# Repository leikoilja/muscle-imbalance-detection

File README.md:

<!-- PROJECT SHIELDS -->
<!--
*** I'm using markdown "reference style" links for readability.
*** Reference links are enclosed in brackets [ ] instead of parentheses ( ).
*** See the bottom of this document for the declaration of the reference variables
*** for contributors-url, forks-url, etc. This is an optional, concise syntax you may use.
*** https://www.markdownguide.org/basic-syntax/#reference-style-links
-->
[![Contributors][contributors-shield]][contributors-url]
[![Forks][forks-shield]][forks-url]
[![Stargazers][stars-shield]][stars-url]
[![Issues][issues-shield]][issues-url]
[![MIT License][license-shield]][license-url]

<!-- PROJECT LOGO -->
<br />
<p align="center">

  <h3 align="center">Muscle Imbalance Detection (MID)</h3>

  <p align="center">
    This project was a part of <a href="https://www.kth.se/">KTH</a> University <a href="https://www.kth.se/student/kurser/kurs/HL2032?l=en">HL2032</a> course to create a medical engineering project.
    <br />
    <a href="https://github.com/leikoilja/muscle-imbalance-detection/tree/master/analytics">Analytics</a>
    &
    <a href="https://github.com/leikoilja/muscle-imbalance-detection/tree/master/electronics">Electronics</a>
    &
    <a href="https://github.com/leikoilja/muscle-imbalance-detection/tree/master/mcu">MCU</a>
    &
    <a href="https://github.com/leikoilja/muscle-imbalance-detection/tree/master/mobile_app">Mobile app</a>
  </p>
</p>

<!-- TABLE OF CONTENTS -->
<details open="open">
  <summary>Table of Contents</summary>
  <ol>
    <li>
      <a href="#about-the-project">About The Project</a>
      <ul>
        <li><a href="#design">Design</a></li>
      </ul>
    </li>
    <li>
      <a href="#getting-started">Getting Started</a>
      <ul>
        <li><a href="#prerequisites">Prerequisites</a></li>
      </ul>
    </li>
    <li><a href="#device-demonstration">Demonstration</a></li>
    <li><a href="#contributing">Contributing</a></li>
    <li><a href="#license">License</a></li>
    <li><a href="#acknowledgements">Acknowledgements</a></li>
  </ol>
</details>

<!-- ABOUT THE PROJECT -->
## About The Project
Patients recovering from knee surgery can have inferior long-term mobility if they do not perform specific rehabilitation exercises soon after surgery. Rehabilitation can fail if the patient does not begin it immediately after surgery, or if they do not have good compliance to the treatment plan. We present a device to assist patients and physicians with visualization of the rehabilitation process, to help them make better decisions about how to tailor a recovery plan. The device can display real time muscle activity feedback using reusable fabric electrodes with equivalent sensitivity to a much more expensive commercial sensor, and store and process the data to provide clinical information.

### Design

The system architecture of data communication is shown in figure 1.
[![Product Name Screen Shot][communication-screenshot]](https://example.com)

#### Electrical and Hardware
The system uses pairs of fabric electrodes integrated into a wearable device to detect muscle activity from the patient. A circuit was implemented to amplify and filter the signals before passing them to a microcontroller, and the EMG signal sensitivity can be adjusted using an integrated potentiometer.
The bluetooth module HC-05 is used to communicate between the signal detection circuit and the mobile application. Data sampling rate is currently set to 1KHz.

#### Mobile applicaton
The mobile app was implemented using React Native open-source mobile application framework. It supports user authentication, Bluetooth connectivity for real-time data monitoring, recording of monitored data, and uploading to cloud computing for further processing. It also allows one to see the archive of previous measurements and their corresponding analysis.

#### Cloud computing
The project utilizes Google firebase product which powers up authentication and cloud data storage functionalities. Firebase was chosen due to its robustness and sensitive data safety.
Backend analysis is implemented using python3.7 open source programming language which is mainly used for EMG signal analysis, filtration, and processing with the data collected from the cloud. The dataset we created from various sources used to recognize muscle recovery over time and muscle fatigue level.

<!-- GETTING STARTED -->
## Getting Started

To get started follow the corresponding sections and their READMEs:
<br />
<a href="https://github.com/leikoilja/muscle-imbalance-detection/tree/master/analytics">Analytics</a>
&
<a href="https://github.com/leikoilja/muscle-imbalance-detection/tree/master/electronics">Electronics</a>
&
<a href="https://github.com/leikoilja/muscle-imbalance-detection/tree/master/mcu">MCU</a>
&
<a href="https://github.com/leikoilja/muscle-imbalance-detection/tree/master/mobile_app">Mobile app</a>

### Prerequisites

- Basic electronics and software development knowledge.
- Wearable electrodes for testing. See [this resource](https://github.com/leikoilja/muscle-imbalance-detection/tree/master/electronics/wearble-electrodes) for instructions how to make one.

## Device demonstration
Click to view the video:

Or download the video [here](images/EMG_Knee_Device_Demo_rev2.mp4)

<!-- CONTRIBUTING -->
## Contributing

Contributions are what make the open source community such an amazing place to be learn, inspire, and create. Any contributions you make are **greatly appreciated**.

1. Fork the Project
2. Create your Feature Branch (`git checkout -b feature/AmazingFeature`)
3. Commit your Changes (`git commit -m 'Add some AmazingFeature'`)
4. Push to the Branch (`git push origin feature/AmazingFeature`)
5. Open a Pull Request

<!-- LICENSE -->
## License

Distributed under the MIT License. See `LICENSE` for more information.

<!-- ACKNOWLEDGEMENTS -->
## Acknowledgements
Initial project authors:
* [Katlinkt](https://github.com/Katlinkt)
* [Behname](https://github.com/Behname)
* [sanjayshiva0109](https://github.com/sanjayshiva0109)
* [Vishnu Narayanan](https://github.com/Vishnu1293)
* [Ilja Leiko](https://github.com/leikoilja)

<!-- MARKDOWN LINKS & IMAGES -->
<!-- https://www.markdownguide.org/basic-syntax/#reference-style-links -->
[contributors-shield]: https://img.shields.io/github/contributors/leikoilja/muscle-imbalance-detection
[contributors-url]: https://github.com/leikoilja/muscle-imbalance-detection/graphs/contributors
[forks-shield]: https://img.shields.io/github/forks/leikoilja/muscle-imbalance-detection
[forks-url]: https://github.com/leikoilja/muscle-imbalance-detection/network/members
[stars-shield]: https://img.shields.io/github/stars/leikoilja/muscle-imbalance-detection
[stars-url]: https://github.com/leikoilja/muscle-imbalance-detection/stargazers
[issues-shield]: https://img.shields.io/github/issues/leikoilja/muscle-imbalance-detection
[issues-url]: https://github.com/leikoilja/muscle-imbalance-detection/issues
[license-shield]: https://img.shields.io/github/license/leikoilja/muscle-imbalance-detection
[license-url]: https://github.com/leikoilja/muscle-imbalance-detection/blob/master/LICENSE
[product-screenshot]: images/screenshot.png
[communication-screenshot]: images/communication.png

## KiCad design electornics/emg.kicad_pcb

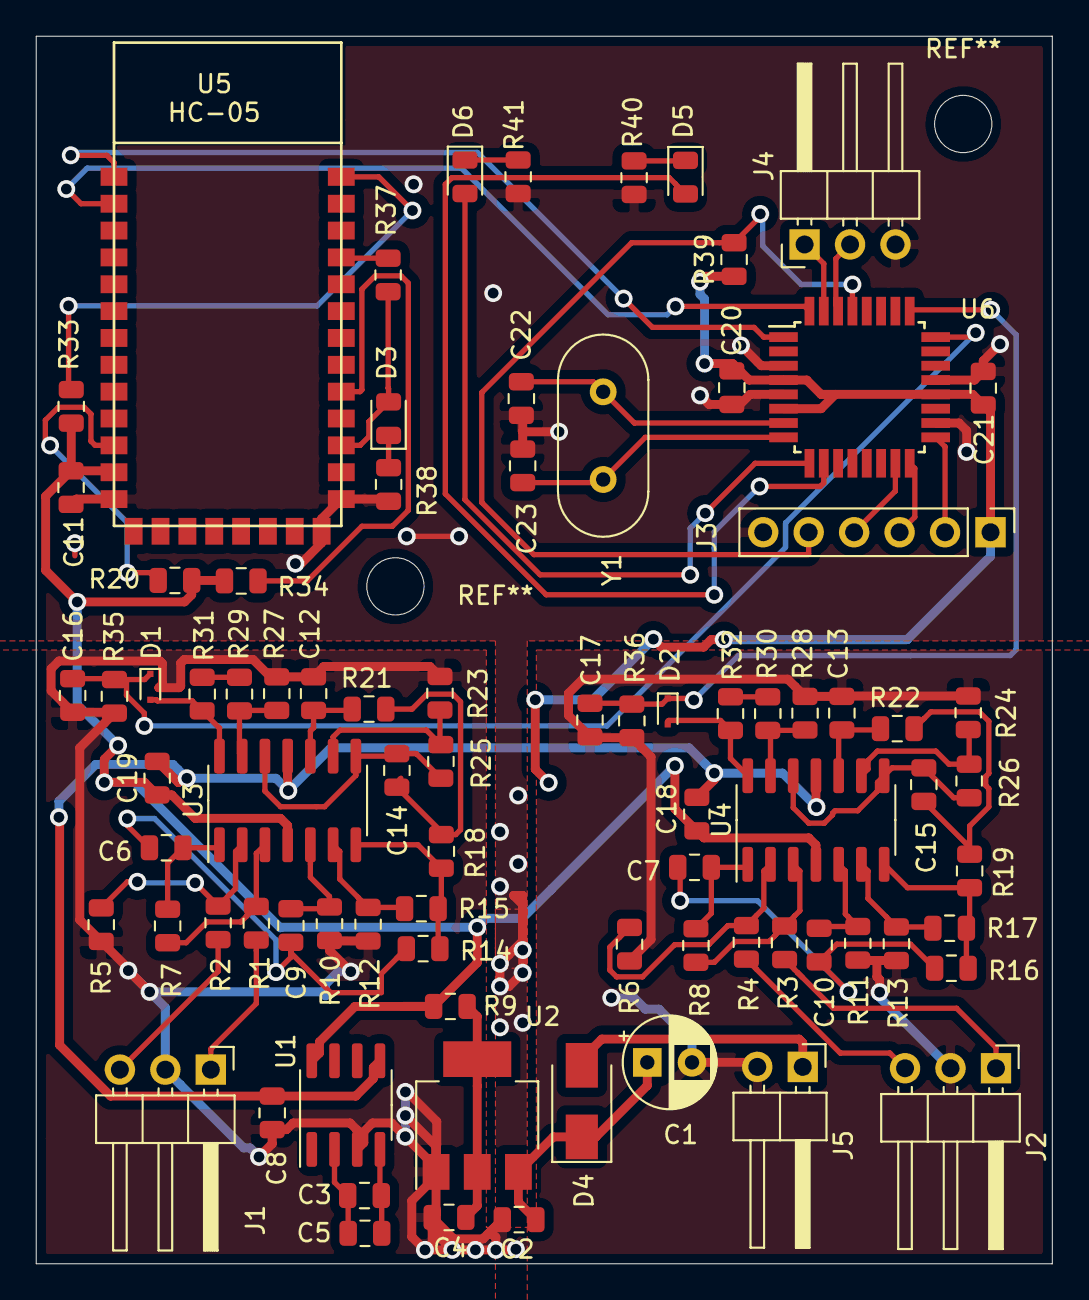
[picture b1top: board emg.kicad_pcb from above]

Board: 2 copper layers, 56.8 x 68.6 mm, 82 parts (0 on the bottom side), 62 nets.

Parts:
C1: C; CP_Radial_D5.0mm_P2.50mm
C2, C3, C4, C5, C6, C7, C8, C9, C10, C11, C12, C13, C14, C15, C16, C17, C18, C19, C20, C21, C22, C23: C; C_0805_2012Metric
D1, D2: 1N4148; D_SC-80
D3, D5, D6: LED; LED_0805_2012Metric
D4: 1N4007; D_SMA
J1, J2, J4: Conn_01x03_Female; PinHeader_1x03_P2.54mm_Horizontal
J3: Conn_01x06_Female; PinHeader_1x06_P2.54mm_Vertical
J5: Conn_01x02_Female; PinHeader_1x02_P2.54mm_Horizontal
R1, R2, R3, R4, R5, R6, R7, R8, R9, R10, R11, R12, R13, R14, R15, R16, R17, R18, R19, R20, R21, R22, R23, R24, R25, R26, R27, R28, R29, R30, R31, R32, R33, R34, R35, R36, R37, R38, R39, R40, R41: R; R_0805_2012Metric
U1: ICL7660; SOIC-8_3.9x4.9mm_P1.27mm
U2: LM1117-3.3; SOT-223-3_TabPin2
U3, U4: LM324; SOIC-14_3.9x8.7mm_P1.27mm
U5: HC-05
U6: ATmega328P-AU; TQFP-32_7x7mm_P0.8mm
Y1: Crystal; Crystal_HC18-U_Vertical

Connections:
+3V3: C11.1, C18.1, C19.1, C20.2, C21.1, J3.1, R9.1, R20.1, R33.1, R34.1, R39.1, U1.8, U3.4, U4.4, U5.12, U6.4, U6.6, U6.20
+5V: C1.1, C2.1, D4.1, U2.3
-3V3: C8.1, C18.2, C19.2, U1.5, U3.11, U4.11
/BRX: U5.2, U6.32
/BTX: U5.1, U6.1
/MISO: J3.3, U6.16
/MOSI: J3.4, U6.15
/NRST: J3.5, R39.2, U6.29
/RXD: J4.2, U6.30
/SCK: J3.2, U6.17
/SENS1: C16.2, D1.1, R35.2, U6.24
/SENS2: C17.2, D2.1, R36.2, U6.25
/TXD: J4.1, U6.31
GND: C1.2, C2.2, C4.2, C8.2, C11.2, C12.1, C13.1, C16.1, C17.1, C20.1, C21.2, C22.2, C23.2, J1.2, J2.2, J3.6, J4.3, J5.2, R5.2, R6.2, R10.1, R11.1, R12.1, R13.1, R23.1, R24.1, R27.1, R28.1, R35.1, R36.1, R38.1, R40.2, R41.2, U1.3, U2.1, U5.13, U5.21, U5.22, U6.3, U6.5, U6.18, U6.21
unnamed: C3.1, C5.1, U1.2
unnamed: C3.2, C5.2, U1.4
unnamed: C4.1, R9.2, U2.2
unnamed: C6.1, R7.1, U3.1
unnamed: C6.2, C9.1, R14.2
unnamed: C7.1, R8.1, U4.1
unnamed: C9.2, R10.2, U3.5
unnamed: C7.2, C10.1, R16.2
unnamed: C10.2, R11.2, U4.5
unnamed: C12.2, R21.1, U3.10
unnamed: C13.2, R22.1, U4.10
unnamed: C14.1, R18.1, R21.2
unnamed: C14.2, R25.2, U3.8, U3.12
unnamed: C15.1, R19.1, R22.2
unnamed: C15.2, R26.2, U4.8, U4.12
unnamed: C22.1, U6.7, Y1.2
unnamed: C23.1, U6.8, Y1.1
unnamed: D1.2, R31.2, U3.14
unnamed: D2.2, R32.2, U4.14
unnamed: D3.1, R38.2
unnamed: D3.2, R37.1, U5.24
unnamed: D4.2, J5.1
unnamed: D5.1, R40.1
unnamed: D5.2, U6.10
unnamed: D6.1, R41.1
unnamed: D6.2, U6.9
unnamed: J1.1, R1.2
unnamed: J1.3, R2.2
unnamed: J2.1, R3.2
unnamed: J2.3, R4.2
unnamed: R1.1, R7.2, U3.3
unnamed: R2.1, R5.1, U3.2
unnamed: R3.1, R8.2, U4.3
unnamed: R4.1, R6.1, U4.2
unnamed: R12.2, R15.1, U3.6
unnamed: R13.2, R17.1, U4.6
unnamed: R14.1, R15.2, R18.2, U3.7
unnamed: R16.1, R17.2, R19.2, U4.7
unnamed: R20.2, U5.11
unnamed: R23.2, R25.1, U3.9
unnamed: R24.2, R26.1, U4.9
unnamed: R27.2, R29.1, U3.13
unnamed: R28.2, R30.1, U4.13
unnamed: R29.2, R31.1
unnamed: R30.2, R32.1
unnamed: R33.2, U5.34
unnamed: R34.2, U5.26
unnamed: R37.2, U5.31

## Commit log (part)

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2020-09-05 Directory structure
2020-09-11 Edited two readme files
2020-09-11 I have uploaded the EMG datas with description below
    https://physionet.org/content/emgdb/1.0.0/
2020-09-21 Personalized greeting by name
2020-09-24 Screen tests implemented
2020-09-26 Removing jest github action for PR
2020-09-26 Bump react-dom from 16.11.0 to 16.13.0 in /mobile_app/mid
    Bumps [react-dom](https://github.com/facebook/react/tree/HEAD/packages/react-dom) from 16.11.0 to 16.13.0.
    - [Release notes](https://github.com/facebook/react/releases)
    - [Changelog](https://github.com/facebook/react/blob/master/CHANGELOG.md)
    - [Commits](https://github.com/facebook/react/commits/v16.13.0/packages/react-dom)
2020-10-01 Expo eject
2020-10-01 Bump babel-preset-expo from 8.1.1 to 8.3.0 in /mobile_app/mid (#10)
    Bumps [babel-preset-expo](https://github.com/expo/expo/tree/HEAD/packages/babel-preset-expo) from 8.1.1 to 8.3.0.
    - [Release notes](https://github.com/expo/expo/releases)
    - [Changelog](https://github.com/expo/expo/blob/master/CHANGELOG.md)
    - [Commits](https://github.com/expo/expo/commits/HEAD/packages/babel-preset-expo)
2020-10-01 Introducing new folder structure (#14)
2020-10-05 Bump @react-navigation/stack from 5.9.0 to 5.9.2 in /mobile_app/mid
    Bumps [@react-navigation/stack](https://github.com/react-navigation/react-navigation/tree/HEAD/packages/stack) from 5.9.0 to 5.9.2.
    - [Release notes](https://github.com/react-navigation/react-navigation/releases)
    - [Changelog](https://github.com/react-navigation/react-navigation/blob/main/packages/stack/CHANGELOG.md)
    - [Commits](https://github.com/react-navigation/react-navigation/commits/@react-navigation/stack@5.9.2/packages/stack)
2020-10-10 Bump react-dom from 16.11.0 to 16.13.0 in /mobile_app/mid (#17)
    Bumps [react-dom](https://github.com/facebook/react/tree/HEAD/packages/react-dom) from 16.11.0 to 16.13.0.
    - [Release notes](https://github.com/facebook/react/releases)
    - [Changelog](https://github.com/facebook/react/blob/master/CHANGELOG.md)
    - [Commits](https://github.com/facebook/react/commits/v16.13.0/packages/react-dom)
2020-10-10 Adding Settings screen
2020-10-10 Bump @types/react from 16.9.49 to 16.9.51 in /mobile_app/mid
    Bumps [@types/react](https://github.com/DefinitelyTyped/DefinitelyTyped/tree/HEAD/types/react) from 16.9.49 to 16.9.51.
    - [Release notes](https://github.com/DefinitelyTyped/DefinitelyTyped/releases)
    - [Commits](https://github.com/DefinitelyTyped/DefinitelyTyped/commits/HEAD/types/react)
2020-10-10 Fixing imroperly configured yest test runner
2020-10-13 Bump eslint from 7.10.0 to 7.11.0 in /mobile_app/mid
    Bumps [eslint](https://github.com/eslint/eslint) from 7.10.0 to 7.11.0.
    - [Release notes](https://github.com/eslint/eslint/releases)
    - [Changelog](https://github.com/eslint/eslint/blob/master/CHANGELOG.md)
    - [Commits](https://github.com/eslint/eslint/compare/v7.10.0...v7.11.0)
2020-10-15 Redux persistancy
2020-10-15 Bump react-native-reanimated from 1.13.0 to 1.13.1 in /mobile_app/mid
    Bumps [react-native-reanimated](https://github.com/software-mansion/react-native-reanimated) from 1.13.0 to 1.13.1.
    - [Release notes](https://github.com/software-mansion/react-native-reanimated/releases)
    - [Commits](https://github.com/software-mansion/react-native-reanimated/compare/1.13.0...1.13.1)
2020-10-16 Uploading recorded data to Firestore
2020-10-19 Bump expo-asset from 8.1.7 to 8.2.0 in /mobile_app/mid
    Bumps [expo-asset](https://github.com/expo/expo/tree/HEAD/packages/expo-asset) from 8.1.7 to 8.2.0.
    - [Release notes](https://github.com/expo/expo/releases)
    - [Changelog](https://github.com/expo/expo/blob/master/packages/expo-asset/CHANGELOG.md)
    - [Commits](https://github.com/expo/expo/commits/HEAD/packages/expo-asset)
2020-11-02 Bump @types/react from 16.9.49 to 16.9.55 in /mobile_app/mid
    Bumps [@types/react](https://github.com/DefinitelyTyped/DefinitelyTyped/tree/HEAD/types/react) from 16.9.49 to 16.9.55.
    - [Release notes](https://github.com/DefinitelyTyped/DefinitelyTyped/releases)
    - [Commits](https://github.com/DefinitelyTyped/DefinitelyTyped/commits/HEAD/types/react)
2020-11-10 Bump expo-updates from 0.2.14 to 0.3.5 in /mobile_app/mid
    Bumps [expo-updates](https://github.com/expo/expo/tree/HEAD/packages/expo-updates) from 0.2.14 to 0.3.5.
    - [Release notes](https://github.com/expo/expo/releases)
    - [Changelog](https://github.com/expo/expo/blob/master/packages/expo-updates/CHANGELOG.md)
    - [Commits](https://github.com/expo/expo/commits/HEAD/packages/expo-updates)
2020-12-14 Bump expo-asset from 8.1.7 to 8.2.1 in /mobile_app/mid
    Bumps [expo-asset](https://github.com/expo/expo/tree/HEAD/packages/expo-asset) from 8.1.7 to 8.2.1.
    - [Release notes](https://github.com/expo/expo/releases)
    - [Changelog](https://github.com/expo/expo/blob/master/packages/expo-asset/CHANGELOG.md)
    - [Commits](https://github.com/expo/expo/commits/HEAD/packages/expo-asset)
2021-01-05 Fixing analytics data parsing
2021-01-06 Adding youtube demo video to the README
2021-01-06 Adding Arduino MCU Readme
2021-01-07 Minor README changes
2021-01-11 Bump @expo/vector-icons from 10.2.1 to 12.0.2 in /mobile_app/mid
    Bumps [@expo/vector-icons](https://github.com/expo/vector-icons) from 10.2.1 to 12.0.2.
    - [Release notes](https://github.com/expo/vector-icons/releases)
    - [Commits](https://github.com/expo/vector-icons/commits)
2021-01-18 Bump react-native-toast-message from 1.3.4 to 1.4.3 in /mobile_app/mid
    Bumps [react-native-toast-message](https://github.com/calintamas/react-native-toast-message) from 1.3.4 to 1.4.3.
    - [Release notes](https://github.com/calintamas/react-native-toast-message/releases)
    - [Changelog](https://github.com/calintamas/react-native-toast-message/blob/master/CHANGELOG.md)
    - [Commits](https://github.com/calintamas/react-native-toast-message/compare/v1.3.4...v1.4.3)
2021-02-22 Bump react-native-toast-message from 1.3.4 to 1.4.7 in /mobile_app/mid
    Bumps [react-native-toast-message](https://github.com/calintamas/react-native-toast-message) from 1.3.4 to 1.4.7.
    - [Release notes](https://github.com/calintamas/react-native-toast-message/releases)
    - [Changelog](https://github.com/calintamas/react-native-toast-message/blob/master/CHANGELOG.md)
    - [Commits](https://github.com/calintamas/react-native-toast-message/compare/v1.3.4...v1.4.7)
2021-03-15 Bump @expo/vector-icons from 10.2.1 to 12.0.4 in /mobile_app/mid
    Bumps [@expo/vector-icons](https://github.com/expo/vector-icons) from 10.2.1 to 12.0.4.
    - [Release notes](https://github.com/expo/vector-icons/releases)
    - [Commits](https://github.com/expo/vector-icons/commits)
2021-04-12 Bump react-native-screens from 2.9.0 to 3.1.0 in /mobile_app/mid
    Bumps [react-native-screens](https://github.com/kmagiera/react-native-screens) from 2.9.0 to 3.1.0.
    - [Release notes](https://github.com/kmagiera/react-native-screens/releases)
    - [Commits](https://github.com/kmagiera/react-native-screens/compare/2.9.0...3.1.0)
2021-05-17 Bump react-native-screens from 2.9.0 to 3.2.0 in /mobile_app/mid
    Bumps [react-native-screens](https://github.com/software-mansion/react-native-screens) from 2.9.0 to 3.2.0.
    - [Release notes](https://github.com/software-mansion/react-native-screens/releases)
    - [Commits](https://github.com/software-mansion/react-native-screens/compare/2.9.0...3.2.0)
2021-08-09 Bump react-native-screens from 2.9.0 to 3.5.0 in /mobile_app/mid
    Bumps [react-native-screens](https://github.com/software-mansion/react-native-screens) from 2.9.0 to 3.5.0.
    - [Release notes](https://github.com/software-mansion/react-native-screens/releases)
    - [Commits](https://github.com/software-mansion/react-native-screens/compare/2.9.0...3.5.0)
    ---
    updated-dependencies:
    - dependency-name: react-native-screens
2021-09-13 Bump react-native-screens from 2.9.0 to 3.7.0 in /mobile_app/mid
    Bumps [react-native-screens](https://github.com/software-mansion/react-native-screens) from 2.9.0 to 3.7.0.
    - [Release notes](https://github.com/software-mansion/react-native-screens/releases)
    - [Commits](https://github.com/software-mansion/react-native-screens/compare/2.9.0...3.7.0)
    ---
    updated-dependencies:
    - dependency-name: react-native-screens
2021-11-01 Bump react-native-screens from 2.9.0 to 3.9.0 in /mobile_app/mid
    Bumps [react-native-screens](https://github.com/software-mansion/react-native-screens) from 2.9.0 to 3.9.0.
    - [Release notes](https://github.com/software-mansion/react-native-screens/releases)
    - [Commits](https://github.com/software-mansion/react-native-screens/compare/2.9.0...3.9.0)
    ---
    updated-dependencies:
    - dependency-name: react-native-screens
2021-12-13 Bump react-native-toast-message from 1.3.4 to 2.1.0 in /mobile_app/mid
    Bumps [react-native-toast-message](https://github.com/calintamas/react-native-toast-message) from 1.3.4 to 2.1.0.
    - [Release notes](https://github.com/calintamas/react-native-toast-message/releases)
    - [Changelog](https://github.com/calintamas/react-native-toast-message/blob/main/CHANGELOG.md)
    - [Commits](https://github.com/calintamas/react-native-toast-message/compare/v1.3.4...v2.1.0)
    ---
    updated-dependencies:
2022-01-24 Bump react-native-screens from 2.9.0 to 3.10.2 in /mobile_app/mid
    Bumps [react-native-screens](https://github.com/software-mansion/react-native-screens) from 2.9.0 to 3.10.2.
    - [Release notes](https://github.com/software-mansion/react-native-screens/releases)
    - [Commits](https://github.com/software-mansion/react-native-screens/compare/2.9.0...3.10.2)
    ---
    updated-dependencies:
    - dependency-name: react-native-screens
2022-02-21 Bump react-native-screens from 2.9.0 to 3.12.0 in /mobile_app/mid
    Bumps [react-native-screens](https://github.com/software-mansion/react-native-screens) from 2.9.0 to 3.12.0.
    - [Release notes](https://github.com/software-mansion/react-native-screens/releases)
    - [Commits](https://github.com/software-mansion/react-native-screens/compare/2.9.0...3.12.0)
    ---
    updated-dependencies:
    - dependency-name: react-native-screens
2022-03-21 Bump react-native from 0.63.3 to 0.67.4 in /mobile_app/mid
    Bumps [react-native](https://github.com/facebook/react-native) from 0.63.3 to 0.67.4.
    - [Release notes](https://github.com/facebook/react-native/releases)
    - [Changelog](https://github.com/facebook/react-native/blob/main/CHANGELOG.md)
    - [Commits](https://github.com/facebook/react-native/compare/v0.63.3...v0.67.4)
    ---
    updated-dependencies:
2022-04-04 Bump react-native from 0.63.3 to 0.68.0 in /mobile_app/mid
    Bumps [react-native](https://github.com/facebook/react-native) from 0.63.3 to 0.68.0.
    - [Release notes](https://github.com/facebook/react-native/releases)
    - [Changelog](https://github.com/facebook/react-native/blob/main/CHANGELOG.md)
    - [Commits](https://github.com/facebook/react-native/compare/v0.63.3...v0.68.0)
    ---
    updated-dependencies:
2022-05-16 Bump react-native from 0.63.3 to 0.68.2 in /mobile_app/mid
    Bumps [react-native](https://github.com/facebook/react-native) from 0.63.3 to 0.68.2.
    - [Release notes](https://github.com/facebook/react-native/releases)
    - [Changelog](https://github.com/facebook/react-native/blob/main/CHANGELOG.md)
    - [Commits](https://github.com/facebook/react-native/compare/v0.63.3...v0.68.2)
    ---
    updated-dependencies:
2022-07-04 Bump react-native-screens from 2.9.0 to 3.14.0 in /mobile_app/mid
    Bumps [react-native-screens](https://github.com/software-mansion/react-native-screens) from 2.9.0 to 3.14.0.
    - [Release notes](https://github.com/software-mansion/react-native-screens/releases)
    - [Commits](https://github.com/software-mansion/react-native-screens/compare/2.9.0...3.14.0)
    ---
    updated-dependencies:
    - dependency-name: react-native-screens
2022-10-10 Bump react-native-screens from 2.9.0 to 3.18.0 in /mobile_app/mid
    Bumps [react-native-screens](https://github.com/software-mansion/react-native-screens) from 2.9.0 to 3.18.0.
    - [Release notes](https://github.com/software-mansion/react-native-screens/releases)
    - [Commits](https://github.com/software-mansion/react-native-screens/compare/2.9.0...3.18.0)
    ---
    updated-dependencies:
    - dependency-name: react-native-screens
